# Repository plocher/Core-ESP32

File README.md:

# Core-ESP32
## License: CERN Open Hardware Licence v1.2

Core Field Unit Processor board using an ESP32 Dev Board with Wifi, BLE and a small OLED screen

  * Uses the [30-pin (2x15) "DEV" package](https://www.ebay.com/itm/333414813426)
  * Includes [C/MRI RS485 interface card](https://spcoast.github.io/pages/CMRI-Bus-Interface.html) IO connection
  * Supports I2C OLED: 1306 based 128x32, 128x64...

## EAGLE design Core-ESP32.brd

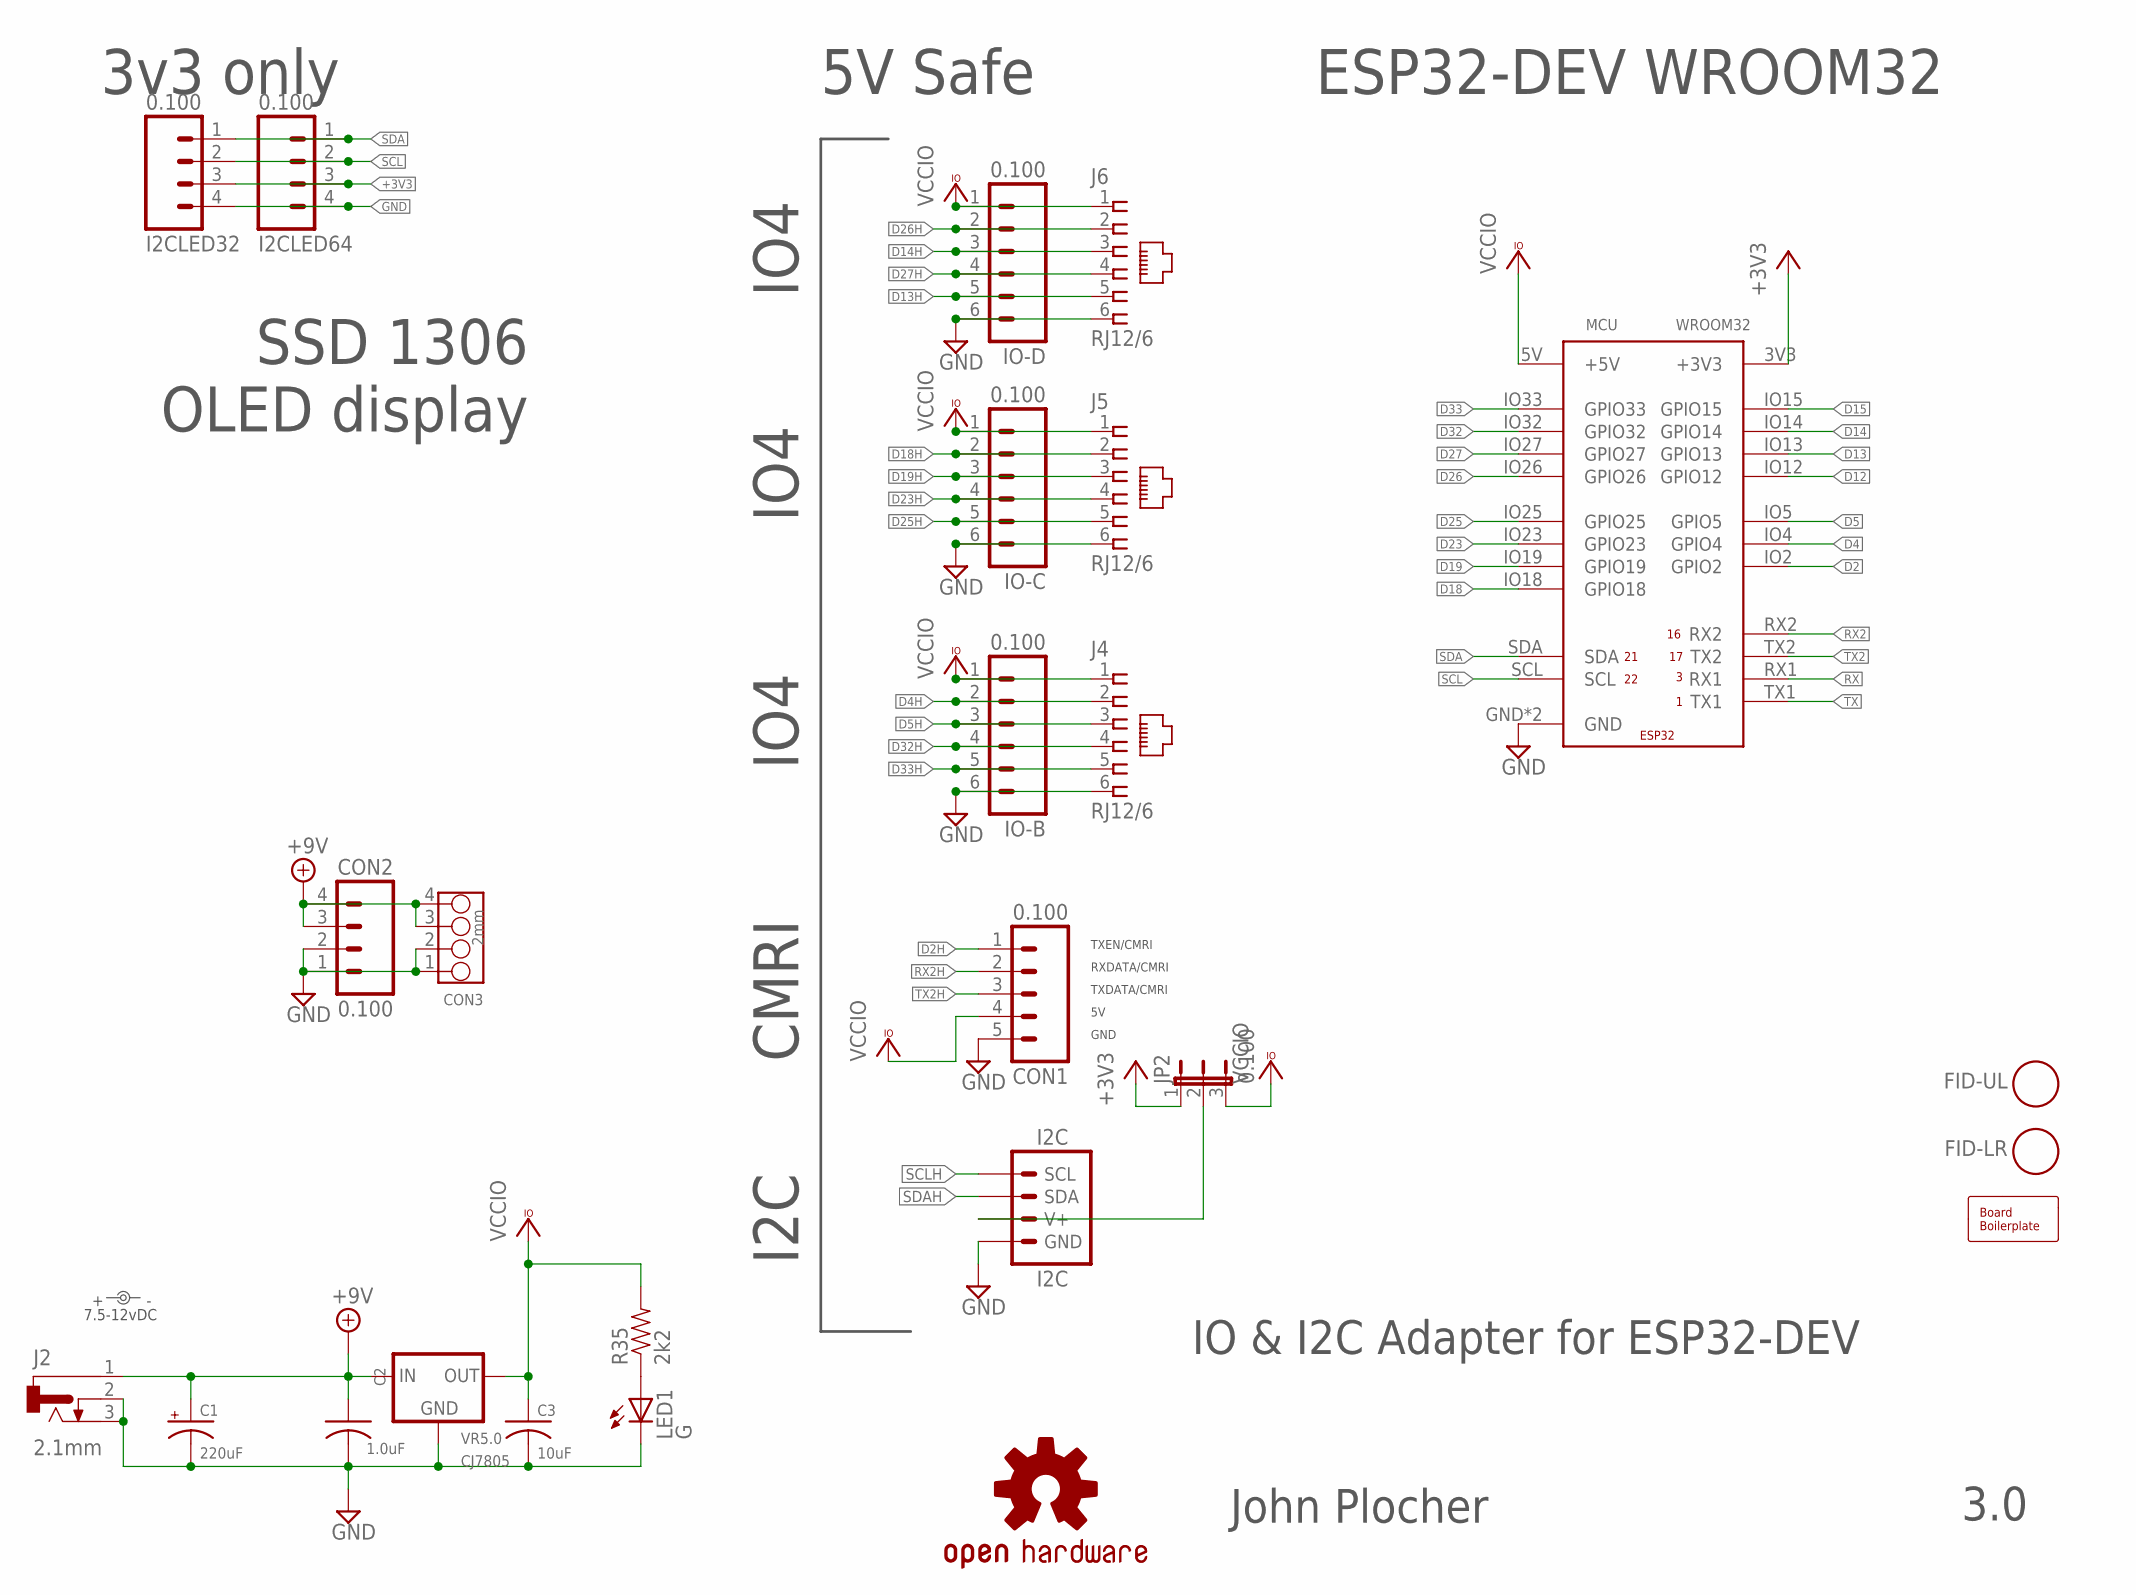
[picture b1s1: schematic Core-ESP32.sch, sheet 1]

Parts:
BOARD: BOARD; BOARD-DINRAIL-3.17IN-IOB
C1: 220uF; 0810-CAP
C2: 1.0uF; 0603-CAP
C3: 10uF; 0603-CAP
CON1: 0.100; 1X05_LOCK
CON2: 0.100; 1X04_LOCK
CON3: 2mm; 4P-2.0
FID-LR: FIDUCIAL; FIDUCIAL_1MM
FID-UL: FIDUCIAL; FIDUCIAL_1MM
I2C: I2C; I2C-L
I2CLED32, I2CLED64: 0.100; 1X04_LOCK
IO-B: 0.100; 1X06_LOCK
IO-C: 0.100; 1X06_LOCK
IO-D: 0.100; 1X06_LOCK
J2: 2.1mm; DCJ0202
J4, J5, J6: RJ12/6; RJ25-INVERTED
JP2: 0.100; 1X03
LABEL1: 7.5-12vDC; PWR_LABEL
LED1: G; 0603-LED
MCU: WROOM32; ESP32-DEV
OSHW1: OSHW; OSHW-LOGO-L
R35: 2k2; 0603-RES
VR5.0: CJ7805; TO-252

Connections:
+3V3: I2CLED32.3, I2CLED64.3, JP2.1, MCU.3V3 (+3V3); also elsewhere on the board
+9V: C1.+, C2.1, CON2.3, CON2.4, CON3.3, CON3.4, J2.1, VR5.0.1 (IN)
D2: MCU.IO2 (GPIO2); also elsewhere on the board
D2H: CON1.1; also elsewhere on the board
D4: MCU.IO4 (GPIO4); also elsewhere on the board
D4H: IO-B.2, J4.2; also elsewhere on the board
D5: MCU.IO5 (GPIO5); also elsewhere on the board
D5H: IO-B.3, J4.3; also elsewhere on the board
D12: MCU.IO12 (GPIO12)
D13: MCU.IO13 (GPIO13); also elsewhere on the board
D13H: IO-D.5, J6.5; also elsewhere on the board
D14: MCU.IO14 (GPIO14); also elsewhere on the board
D14H: IO-D.3, J6.3; also elsewhere on the board
D15: MCU.IO15 (GPIO15)
D18: MCU.IO18 (GPIO18); also elsewhere on the board
D18H: IO-C.2, J5.2; also elsewhere on the board
D19: MCU.IO19 (GPIO19); also elsewhere on the board
D19H: IO-C.3, J5.3; also elsewhere on the board
D23: MCU.IO23 (GPIO23); also elsewhere on the board
D23H: IO-C.4, J5.4; also elsewhere on the board
D25: MCU.IO25 (GPIO25); also elsewhere on the board
D25H: IO-C.5, J5.5; also elsewhere on the board
D26: MCU.IO26 (GPIO26); also elsewhere on the board
D26H: IO-D.2, J6.2; also elsewhere on the board
D27: MCU.IO27 (GPIO27); also elsewhere on the board
D27H: IO-D.4, J6.4; also elsewhere on the board
D32: MCU.IO32 (GPIO32); also elsewhere on the board
D32H: IO-B.4, J4.4; also elsewhere on the board
D33: MCU.IO33 (GPIO33); also elsewhere on the board
D33H: IO-B.5, J4.5; also elsewhere on the board
GND: C1.-, C2.2, C3.2, CON1.5, CON2.1, CON2.2, CON3.1, CON3.2, I2C.GND, I2C.GND@1 (GND), I2CLED32.4, I2CLED64.4, IO-B.6, IO-C.6, IO-D.6, J2.2, J2.3, J4.6, J5.6, J6.6, LED1.C, MCU.GND, MCU.GND@1 (GND), VR5.0.2 (GND)
unnamed: LED1.A, R35.1
unnamed: I2C.V+, I2C.V+@1 (V+), JP2.2
RX: MCU.RX1
RX2: MCU.RX2; also elsewhere on the board
RX2H: CON1.2; also elsewhere on the board
SCL: I2CLED32.2, I2CLED64.2, MCU.SCL; also elsewhere on the board
SCLH: I2C.SCL, I2C.SCL@1 (SCL); also elsewhere on the board
SDA: I2CLED32.1, I2CLED64.1, MCU.SDA; also elsewhere on the board
SDAH: I2C.SDA, I2C.SDA@1 (SDA); also elsewhere on the board
TX: MCU.TX1
TX2: MCU.TX2; also elsewhere on the board
TX2H: CON1.3; also elsewhere on the board
VCCIO: C3.1, CON1.4, IO-B.1, IO-C.1, IO-D.1, J4.1, J5.1, J6.1, JP2.3, MCU.5V (+5V), R35.2, VR5.0.3 (OUT); also elsewhere on the board

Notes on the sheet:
IO & I2C Adapter for ESP32-DEV
John Plocher
3.0
I2C
ESP32-DEV WROOM32
IO4
5V Safe
CMRI
TXEN/CMRI
RXDATA/CMRI
TXDATA/CMRI
GND
3v3 only
SSD 1306 OLED display

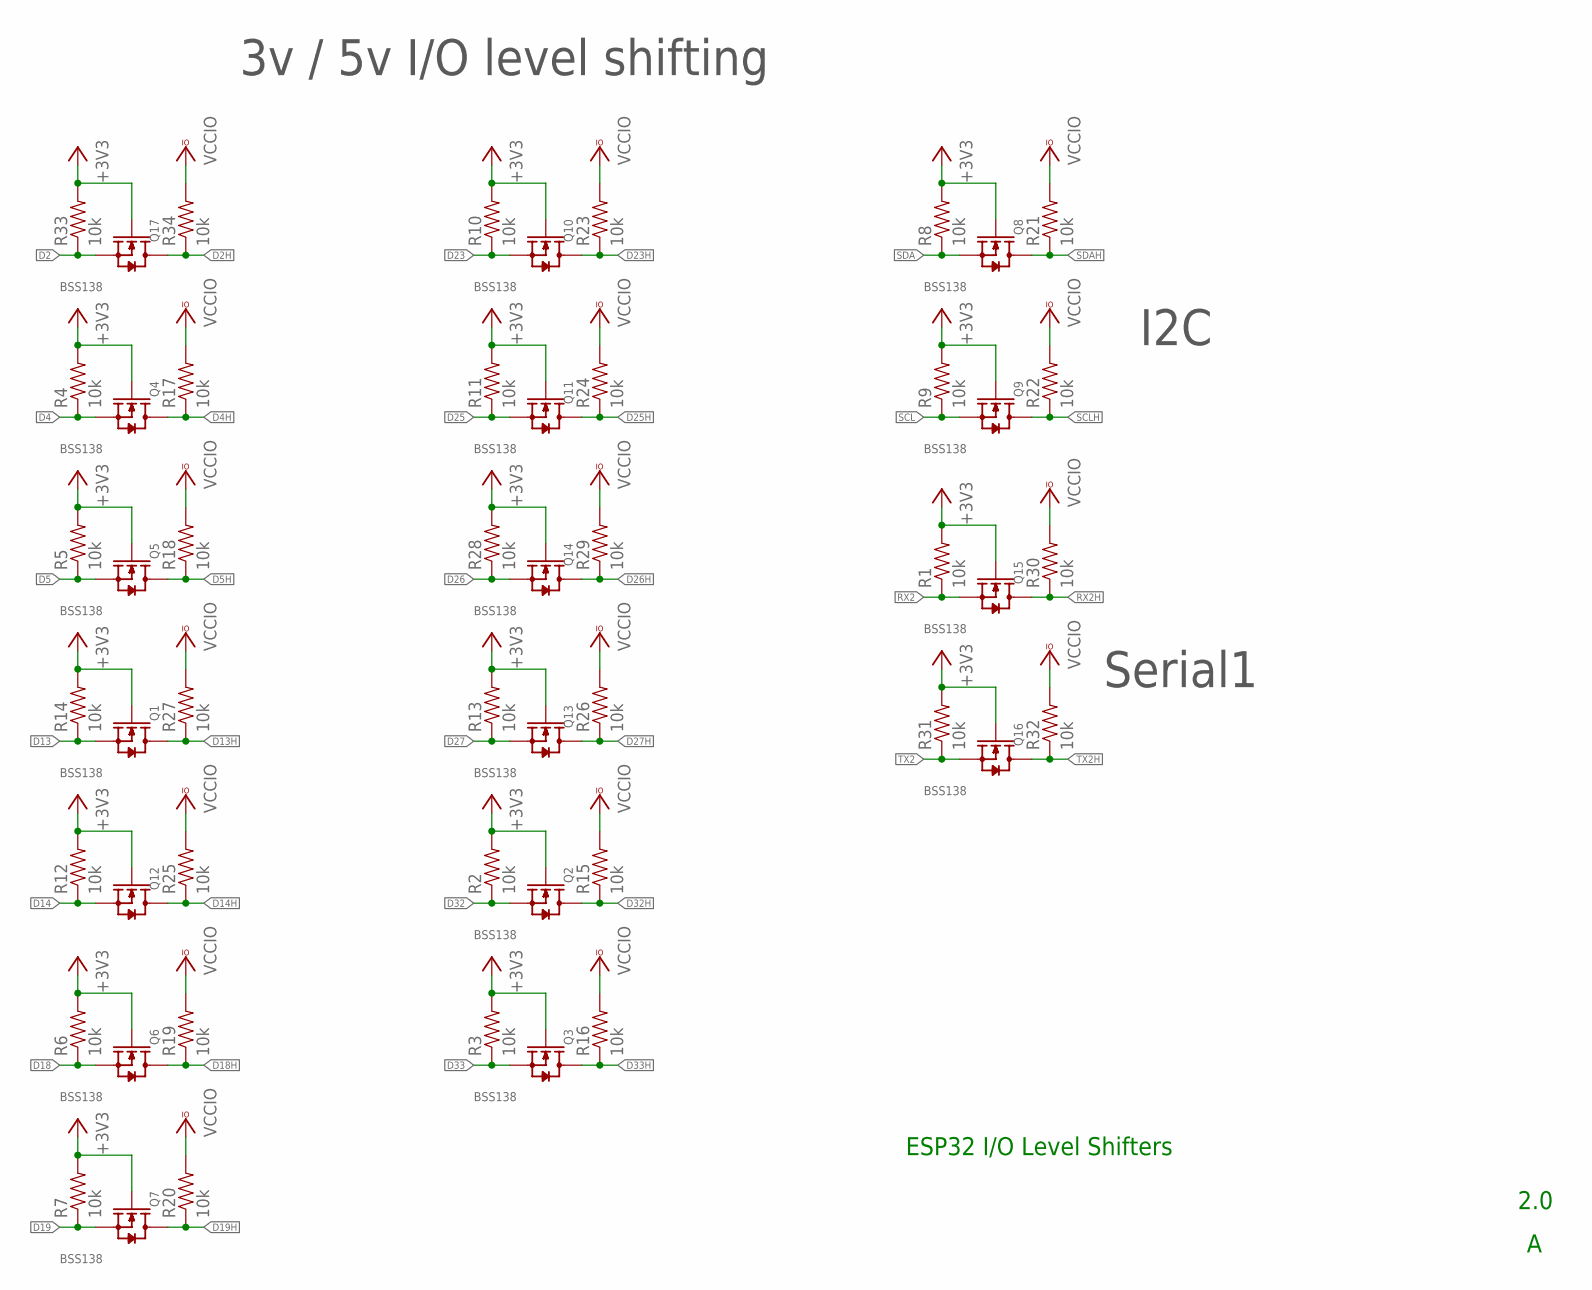
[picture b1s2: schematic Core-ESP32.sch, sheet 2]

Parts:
Q1, Q2, Q3, Q4, Q5, Q6, Q7, Q8, Q9, Q10, Q11, Q12, Q13, Q14, Q15, Q16, Q17: BSS138; SOT23
R1, R2, R3, R4, R5, R6, R7, R8, R9, R10, R11, R12, R13, R14, R15, R16, R17, R18, R19, R20, R21, R22, R23, R24, R25, R26, R27, R28, R29, R30, R31, R32, R33, R34: 10k; 0603-RES

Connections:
+3V3: Q1.1 (G), Q2.1 (G), Q3.1 (G), Q4.1 (G), Q5.1 (G), Q6.1 (G), Q7.1 (G), Q8.1 (G), Q9.1 (G), Q10.1 (G), Q11.1 (G), Q12.1 (G), Q13.1 (G), Q14.1 (G), Q15.1 (G), Q16.1 (G), Q17.1 (G), R1.2, R2.2, R3.2, R4.2, R5.2, R6.2, R7.2, R8.2, R9.2, R10.2, R11.2, R12.2, R13.2, R14.2, R28.2, R31.2, R33.2; also elsewhere on the board
D2: Q17.2 (S), R33.1; also elsewhere on the board
D2H: Q17.3 (D), R34.1; also elsewhere on the board
D4: Q4.2 (S), R4.1; also elsewhere on the board
D4H: Q4.3 (D), R17.1; also elsewhere on the board
D5: Q5.2 (S), R5.1; also elsewhere on the board
D5H: Q5.3 (D), R18.1; also elsewhere on the board
D13: Q1.2 (S), R14.1; also elsewhere on the board
D13H: Q1.3 (D), R27.1; also elsewhere on the board
D14: Q12.2 (S), R12.1; also elsewhere on the board
D14H: Q12.3 (D), R25.1; also elsewhere on the board
D18: Q6.2 (S), R6.1; also elsewhere on the board
D18H: Q6.3 (D), R19.1; also elsewhere on the board
D19: Q7.2 (S), R7.1; also elsewhere on the board
D19H: Q7.3 (D), R20.1; also elsewhere on the board
D23: Q10.2 (S), R10.1; also elsewhere on the board
D23H: Q10.3 (D), R23.1; also elsewhere on the board
D25: Q11.2 (S), R11.1; also elsewhere on the board
D25H: Q11.3 (D), R24.1; also elsewhere on the board
D26: Q14.2 (S), R28.1; also elsewhere on the board
D26H: Q14.3 (D), R29.1; also elsewhere on the board
D27: Q13.2 (S), R13.1; also elsewhere on the board
D27H: Q13.3 (D), R26.1; also elsewhere on the board
D32: Q2.2 (S), R2.1; also elsewhere on the board
D32H: Q2.3 (D), R15.1; also elsewhere on the board
D33: Q3.2 (S), R3.1; also elsewhere on the board
D33H: Q3.3 (D), R16.1; also elsewhere on the board
RX2: Q15.2 (S), R1.1; also elsewhere on the board
RX2H: Q15.3 (D), R30.1; also elsewhere on the board
SCL: Q9.2 (S), R9.1; also elsewhere on the board
SCLH: Q9.3 (D), R22.1; also elsewhere on the board
SDA: Q8.2 (S), R8.1; also elsewhere on the board
SDAH: Q8.3 (D), R21.1; also elsewhere on the board
TX2: Q16.2 (S), R31.1; also elsewhere on the board
TX2H: Q16.3 (D), R32.1; also elsewhere on the board
VCCIO: R15.2, R16.2, R17.2, R18.2, R19.2, R20.2, R21.2, R22.2, R23.2, R24.2, R25.2, R26.2, R27.2, R29.2, R30.2, R32.2, R34.2; also elsewhere on the board

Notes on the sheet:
ESP32 I/O Level Shifters
2.0
3v / 5v I/O level shifting
I2C
Serial1

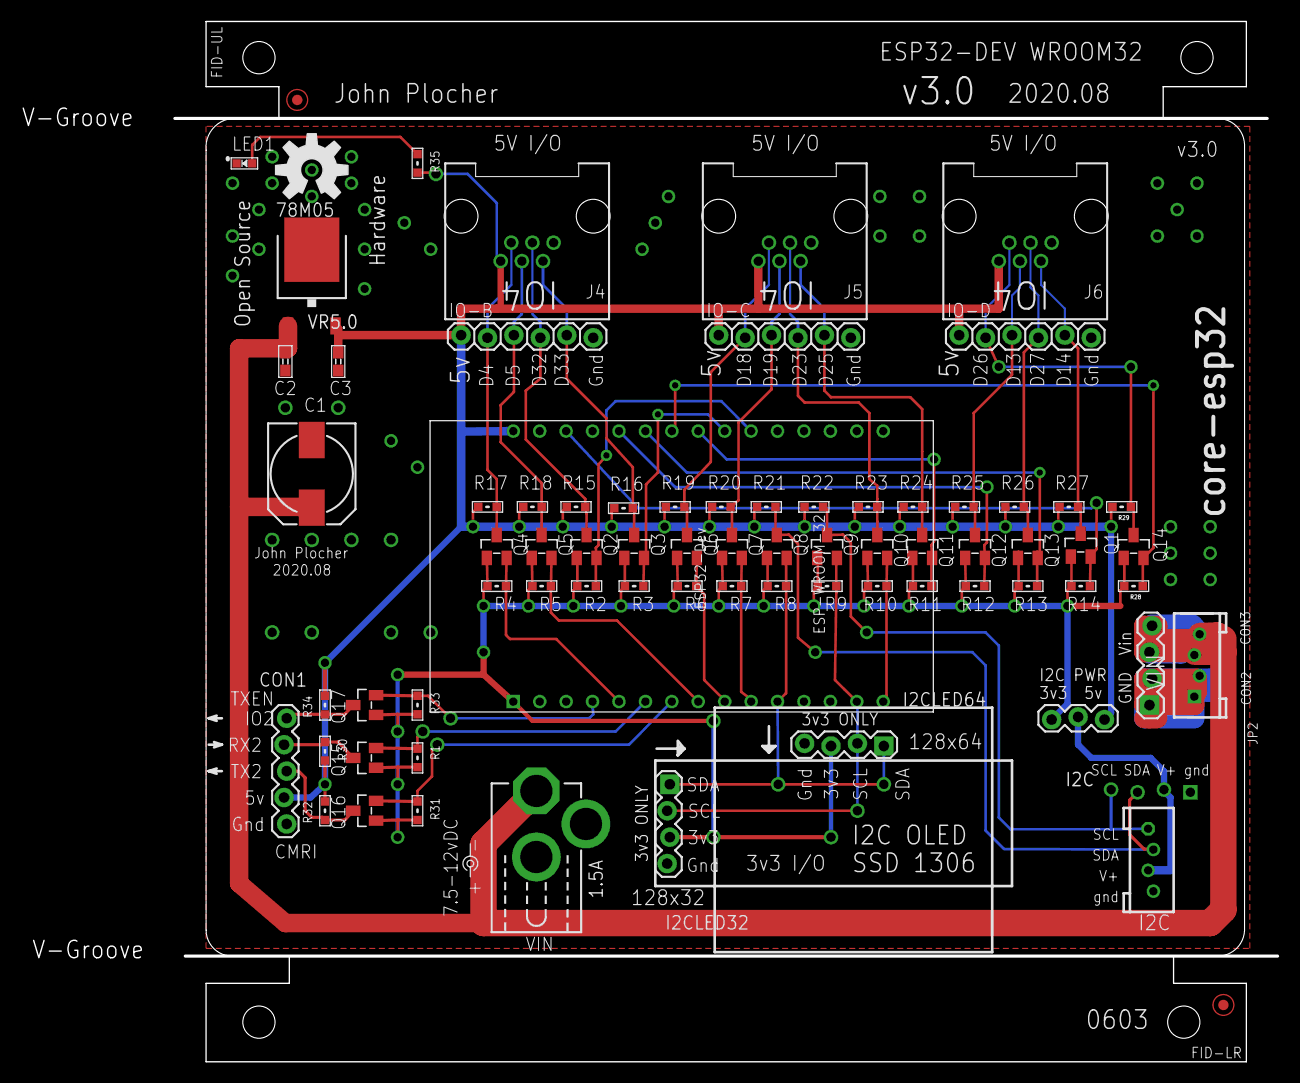
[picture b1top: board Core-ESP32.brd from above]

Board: 2 copper layers, 106.0 x 100.0 mm, 77 parts (0 on the bottom side), 40 nets.

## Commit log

2019-12-09 added graphic
2020-03-07 switched to 30-pin dev board from larger Geekreit one
2020-05-04 updated tags
2020-05-04 cleanup
2020-08-06 convert to 30-pin DEV board, add CMRI-net IO
2020-08-12 SPCoast lbr footprint update
2020-10-05 added values for connectors
2020-10-06 normalized values
